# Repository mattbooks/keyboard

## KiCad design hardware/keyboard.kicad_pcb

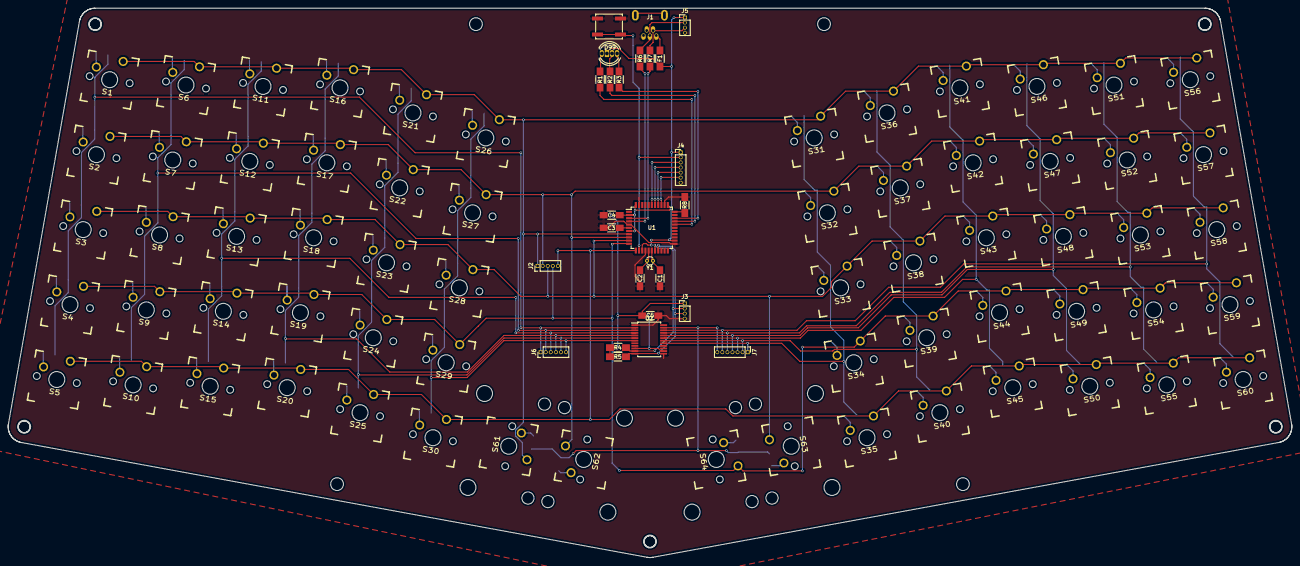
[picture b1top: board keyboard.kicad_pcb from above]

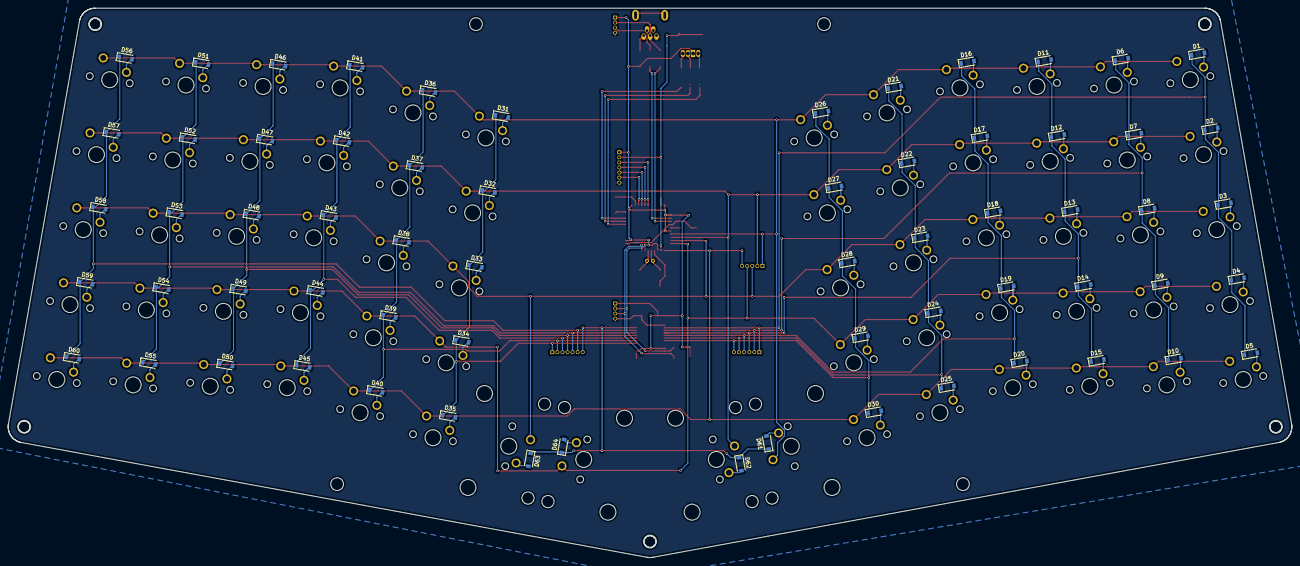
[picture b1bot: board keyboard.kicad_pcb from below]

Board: 2 copper layers, 321.3 x 137.5 mm, 154 parts (64 on the bottom side), 106 nets.

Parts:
C1, C2: 18pF; C_1206_HandSoldering
C3: 1uF; C_1206_HandSoldering
C4, C5: 100nF; C_1206_HandSoldering
D1, D2, D3, D4, D5, D6, D7, D8, D9, D10, D11, D12, D13, D14, D15, D16, D17, D18, D19, D20, D21, D22, D23, D24, D25, D26, D27, D28, D29, D30, D31, D32, D33, D34, D35, D36, D37, D38, D39, D40, D41, D42, D43, D44, D45, D46, D47, D48, D49, D50, D51, D52, D53, D54, D55, D56, D57, D58, D59, D60, D61, D62, D63, D64: D_Small; D_SOD-123
D99: LED_ARGB; LED_D5.0mm-4-v2
F1: Polyfuse_Small; R_1206_HandSoldering
J1: USB_OTG; USB-MINI
J2: CONN_01X05; Pin_Header_Straight_1x05_Pitch1.27mm
J3, J5: CONN_01X04; Pin_Header_Straight_1x04_Pitch1.27mm
J4, J7: CONN_01X07; Pin_Header_Straight_1x07_Pitch1.27mm
J6: CONN_01X06; Pin_Header_Straight_1x06_Pitch1.27mm
R1, R2, R3, R8: 1k; R_1206_HandSoldering
R4, R5: 2k2; R_1206_HandSoldering
R6, R7: 22; R_1206_HandSoldering
S1, S2, S3, S4, S5, S6, S7, S8, S9, S10, S11, S12, S13, S14, S15, S16, S17, S18, S19, S20, S21, S22, S23, S24, S25, S26, S27, S28, S29, S30, S31, S32, S33, S34, S35, S36, S37, S38, S39, S40, S41, S42, S43, S44, S45, S46, S47, S48, S49, S50, S51, S52, S53, S54, S55, S56, S57, S58, S59, S60: SPST; CHERRY_PCB_100H
S61, S62, S63, S64: SPST; CHERRY_PCB_200V
S100: SPST; SW_SPST_EVQP0
U1: ATMEGA32U4-AU; TQFP-44_10x10mm_Pitch0.8mm
U2: MCP23018_SSOP; SSOP-24_5.3x8.2mm_Pitch0.65mm
Y1: 16MHz; Crystal_Round_d1.0mm_Vertical

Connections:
+5V: C4.1, C5.1, D99.1, F1.1, J3.1, J4.1, J5.1, R4.1, R5.1, U1.2, U1.7, U1.14, U1.24, U1.34, U1.44, U2.10, U2.14
/D+: J1.3, J5.2, R6.2
/D-: J1.2, J5.3, R7.2
/PE2: R8.2, U1.33
/PF4: J4.3, U1.39
/PF5: J4.4, U1.38
/PF6: J4.5, U1.37
/PF7: J4.6, U1.36
/RESET: J4.2, S100.2, U1.13
COL0: D1.1, D2.1, D3.1, D4.1, D5.1, J6.1, U2.2
COL1: D6.1, D7.1, D8.1, D9.1, D10.1, J6.2, U2.3
COL2: D11.1, D12.1, D13.1, D14.1, D15.1, J6.3, U2.4
COL3: D16.1, D17.1, D18.1, D19.1, D20.1, J6.4, U2.5
COL4: D21.1, D22.1, D23.1, D24.1, D25.1, J6.5, U2.6
COL5: D26.1, D27.1, D28.1, D29.1, D30.1, J6.6, U2.7
COL6: D31.1, D32.1, D33.1, D34.1, D35.1, J7.1, U2.17
COL7: D36.1, D37.1, D38.1, D39.1, D40.1, J7.2, U2.18
COL8: D41.1, D42.1, D43.1, D44.1, D45.1, J7.3, U2.19
COL9: D46.1, D47.1, D48.1, D49.1, D50.1, J7.4, U2.20
COL10: D51.1, D52.1, D53.1, D54.1, D55.1, J7.5, U2.21
COL11: D56.1, D57.1, D58.1, D59.1, D60.1, J7.6, U2.22
COL12: D61.1, D62.1, D63.1, D64.1, J7.7, U2.23
GND: C1.2, C2.2, C3.2, C4.2, C5.2, J1.5, J3.4, J4.7, J5.4, R8.1, S100.1, U1.5, U1.15, U1.23, U1.35, U1.43, U2.1, U2.13
LED1: R1.2, U1.29
LED2: R2.2, U1.30
LED3: R3.2, U1.31
unnamed: C1.1, U1.17, Y1.1
unnamed: C2.1, U1.16, Y1.2
unnamed: C3.1, U1.6
unnamed: D1.2, S1.2
unnamed: D2.2, S2.2
unnamed: D3.2, S3.2
unnamed: D4.2, S4.2
unnamed: D5.2, S5.2
unnamed: D6.2, S6.2
unnamed: D7.2, S7.2
unnamed: D8.2, S8.2
unnamed: D9.2, S9.2
unnamed: D10.2, S10.2
unnamed: D11.2, S11.2
unnamed: D12.2, S12.2
unnamed: D13.2, S13.2
unnamed: D14.2, S14.2
unnamed: D15.2, S15.2
unnamed: D16.2, S16.2
unnamed: D17.2, S17.2
unnamed: D18.2, S18.2
unnamed: D19.2, S19.2
unnamed: D20.2, S20.2
unnamed: D21.2, S21.2
unnamed: D22.2, S22.2
unnamed: D23.2, S23.2
unnamed: D24.2, S24.2
unnamed: D25.2, S25.2
unnamed: D26.2, S26.2
unnamed: D27.2, S27.2
unnamed: D28.2, S28.2
unnamed: D29.2, S29.2
unnamed: D30.2, S30.2
unnamed: D31.2, S31.2
unnamed: D32.2, S32.2
unnamed: D33.2, S33.2
unnamed: D34.2, S34.2
unnamed: D35.2, S35.2
unnamed: D36.2, S36.2
unnamed: D37.2, S37.2
unnamed: D38.2, S38.2
unnamed: D39.2, S39.2
unnamed: D40.2, S40.2
unnamed: D41.2, S41.2
unnamed: D42.2, S42.2
unnamed: D43.2, S43.2
unnamed: D44.2, S44.2
unnamed: D45.2, S45.2
unnamed: D46.2, S46.2
unnamed: D47.2, S47.2
unnamed: D48.2, S48.2
unnamed: D49.2, S49.2
unnamed: D50.2, S50.2
unnamed: D51.2, S51.2
unnamed: D52.2, S52.2
unnamed: D53.2, S53.2
unnamed: D54.2, S54.2
unnamed: D55.2, S55.2
unnamed: D56.2, S56.2
unnamed: D57.2, S57.2
unnamed: D58.2, S58.2
unnamed: D59.2, S59.2
unnamed: D60.2, S60.2
unnamed: D61.2, S61.2
unnamed: D62.2, S62.2
unnamed: D63.2, S63.2
unnamed: D64.2, S64.2
unnamed: D99.2, R1.1
unnamed: D99.3, R2.1
unnamed: D99.4, R3.1
unnamed: F1.2, J1.1
unnamed: R6.1, U1.4
unnamed: R7.1, U1.3
ROW0: J2.1, S1.1, S6.1, S11.1, S16.1, S21.1, S26.1, S31.1, S36.1, S41.1, S46.1, S51.1, S56.1, S61.1, U1.8
ROW1: J2.2, S2.1, S7.1, S12.1, S17.1, S22.1, S27.1, S32.1, S37.1, S42.1, S47.1, S52.1, S57.1, S62.1, U1.9
ROW2: J2.3, S3.1, S8.1, S13.1, S18.1, S23.1, S28.1, S33.1, S38.1, S43.1, S48.1, S53.1, S58.1, S63.1, U1.10
ROW3: J2.4, S4.1, S9.1, S14.1, S19.1, S24.1, S29.1, S34.1, S39.1, S44.1, S49.1, S54.1, S59.1, S64.1, U1.11
ROW4: J2.5, S5.1, S10.1, S15.1, S20.1, S25.1, S30.1, S35.1, S40.1, S45.1, S50.1, S55.1, S60.1, U1.12
SCL: J3.2, R4.2, U1.18, U2.11
SDA: J3.3, R5.2, U1.19, U2.12

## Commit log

2017-03-30 Init hardware
2017-03-31 Add first pass at hardware layout
2017-04-09 keyboard plate prototypes
2017-04-10 Progress on circuit design
2017-06-13 WIP schematic + PCB design
2017-06-14 Extract keys into sheets, add MCP23018
2017-06-24 Add HWB, breakouts, LED to sch
2017-06-24 Start script for placing keys
2017-06-25 Move diodes in script, add big thumb buttons
2017-06-25 Start layout of right hand
2017-06-25 Don't flip diodes if already on B.Cu
2017-06-28 Replace 1.5u with 2u thumb keys
2017-07-01 Fix diodes, Add board edge
2017-07-02 Update expansion pads to be SMD
2017-07-02 Add 3d models
2017-07-02 Add rendering
2017-07-04 Start to lay out components
2017-07-06 Start routing
2017-07-09 More routing
2017-07-17 more routing progress
2017-07-17 check in tweaks to keyboard-modules
2017-07-17 Remove renderings
2017-07-17 Update parts after starting sourcing
2017-07-17 Routing tweaks
2017-07-17 Add GND pours
2017-07-17 Stuffffff
2017-07-17 Mounting holes - need alignment
2017-07-19 Fix mounting holes
2017-07-29 Added logo
2017-07-31 Shrink SSOP pads to accomodate .25 mm spacing
2017-08-13 WIP for V2 fixes
2017-08-14 More WIP on V2
2017-08-14 ignore idea files
2017-11-13 Add more mounting holes, re-route updated components
2017-11-13 Add ground fills
2017-11-13 Update mounting hole references to ''
2017-11-13 Ignore .idea
2017-11-26 finish V2
2017-11-26 Create LICENSE
2017-12-04 Update schematic, WIP fixes + adding test points
2017-12-04 WIP firmware
2017-12-05 update-firmware-revision
2017-12-05 Add mounting holes back
2017-12-09 PCB revisions - more test points and fixes
2017-12-09 Update firmware repo version
2018-03-24 wip-keyboard
2018-04-01 Update board outline and fix some connections
2018-04-01 Update base plate designs
2018-04-01 Equal spacing for mounting holes and fill PCB ground
2018-04-02 Update plate
2018-04-14 Update base plate for tapping insted of bolting
2018-04-14 Update build files
2018-04-14 Tweak settings
